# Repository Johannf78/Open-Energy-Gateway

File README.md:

# AmpX Open Energy Gateway

A comprehensive ESP32-based energy monitoring gateway that communicates with Meatrol Brand energy meters via Modbus protocols (RS485 and TCP/IP). The system collects data from up to 32 meters simultaneously, displays it through a web interface, and uploads measurements to a remote API for centralized monitoring.

**Buy ready-built hardware:** <a href="https://ampx.co/product/ampx-energy-gateway/" target="_blank" rel="noopener noreferrer">AmpX Energy Gateway</a> on ampx.co — DIN-rail unit with WiFi, RS485 or TCP/IP Modbus, and uploads to <a href="https://ampx.app" target="_blank" rel="noopener noreferrer">ampx.app</a>.

## 🌟 Features

### Core Capabilities
- **Multi-Protocol Support**: Compatible with both Modbus RS485 and Modbus TCP/IP communication
- **Multi-Meter Support**: Monitor up to 32 energy meters simultaneously
- **Real-Time Web Interface**: Live data display with WebSocket updates
- **API Integration**: Automatic data upload to AmpX Portal every 30 seconds
- **Auto-Discovery**: Automatic detection of connected meters
- **Dual Hardware Variants**: Separate builds for RS485 and TCP/IP configurations

### Hardware Integration
- **ESP32 Wroom 32U**: Main microcontroller platform
- **RS485 Interface**: MAX485 module for serial communication
- **Ethernet Interface**: W5500 Lite for TCP/IP communication
- **Status Indicators**: Four LEDs for system status monitoring
- **WiFi Support**: Wireless connectivity with WiFiManager

### Data Management
- **Real-Time Monitoring**: 3-second update intervals for web interface
- **Scheduled Uploads**: 30-second intervals for API data transmission
- **JSON Data Format**: Structured data exchange and storage
- **Meter Identification**: Unique serial number tracking for each meter

## ☁️ AmpX Energy Portal

View gateway and meter data in the cloud at <a href="https://ampx.app/" target="_blank" rel="noopener noreferrer">https://ampx.app/</a>.

The portal lets you manage gateways, inspect live and historical readings (voltage, current, power, and energy per phase), and export CSV for reporting. The firmware uploads a timestamped snapshot about every 30 seconds.

The portal can be **white-labelled** for your company or resellers (your branding, your domain). Data can also be **customised** and sent to **any portal or platform**, in **any format** you require. Contact AmpX if you need a branded instance or a custom integration.

## 🏗️ Architecture

```
┌─────────────────┐    ┌──────────────────┐    ┌─────────────────┐
│   Energy Meters │    │  AmpX Gateway    │    │   AmpX Portal   │
│                 │    │                  │    │                 │
│ Meatrol Meters  │◄──►│ ESP32 + Modbus   │◄──►│ Remote API      │
│ (RS485/TCP-IP)  │    │ Web Interface    │    │ Data Storage    │
│ Up to 32 units  │    │ Data Processing  │    │ Analytics       │
└─────────────────┘    └──────────────────┘    └─────────────────┘
```

## 📋 Hardware Requirements

### Base Components
- **ESP32 Wroom 32U** microcontroller
- **Power Supply**: 3.3V regulated power
- **Status LEDs**: 5x LEDs for system monitoring (Power, Meter, WiFi, Internet, Server)

### RS485 Configuration
- **MAX485 Interface Module**
- **RS485 Cable**: For meter communication
- **Pull-up/Pull-down Resistors**: 120Ω termination resistors

### TCP/IP Configuration
- **W5500 Lite Ethernet Module**
- **Ethernet Cable**: CAT5/CAT6 network connection
- **Network Switch/Router**: For meter and internet connectivity

## 🚀 Installation

### Prerequisites
- [Arduino IDE](https://www.arduino.cc/en/software) (recommended)
- In Arduino IDE, add this under `File -> Preferences -> Additional Board Manager URLs`:  
  `https://raw.githubusercontent.com/espressif/arduino-esp32/gh-pages/package_esp32_index.json`
  Then install `esp32` from `Tools -> Board -> Boards Manager`.
- ESP32 Board Package for Arduino IDE
- USB-to-UART driver for your ESP32 board (CP210x VCP driver): [Silicon Labs CP210x USB to UART Bridge VCP Drivers](https://www.silabs.com/developers/usb-to-uart-bridge-vcp-drivers)
- Required Arduino libraries (see Dependencies section)

### Quick Start

1. **Clone the Repository**
   ```bash
   git clone https://github.com/Johannf78/Open-Energy-Gateway.git
   cd Open-Energy-Gateway
   ```

2. **Open the Project**
   - **Arduino IDE** (recommended): Open `src/open_energy_gateway/open_energy_gateway.ino`
   - Alternative - PlatformIO: Open the project folder

3. **Configure Hardware Type**
   
   In `open_energy_gateway.ino`, set the communication type:
   ```cpp
   #define MODBUS_TYPE MODBUS_TYPE_RS485  // For RS485 version
   // OR
   #define MODBUS_TYPE MODBUS_TYPE_TCPIP  // For TCP/IP version
   ```

4. **Install USB Driver (Required)**
   - Most ESP32 development boards use a CP210x USB-to-UART bridge chip
   - Install the CP210x VCP driver from Silicon Labs:  
     [https://www.silabs.com/developers/usb-to-uart-bridge-vcp-drivers](https://www.silabs.com/developers/usb-to-uart-bridge-vcp-drivers)
   - On the Silicon Labs download list (Windows), select **CP210x Windows Drivers**
   - Reconnect the board after driver installation so the serial COM port is detected

5. **Upload to ESP32**
   - Connect your ESP32 via USB
   - Select the correct board and port
   - Compile and upload the code

### Dependencies

The following libraries are required:
```cpp
#include <WiFi.h>              // ESP32 built-in WiFi
#include <WebServer.h>         // ESP32 built-in web server
#include <WebSocketsServer.h>  // Real-time updates (by Markus Sattler)
#include <ArduinoJson.h>       // JSON processing (by Benoit Blanchon)
#include <HTTPClient.h>        // ESP32 built-in HTTP client
#include <WiFiManager.h>       // WiFi configuration (by tzapu)
#include <Preferences.h>       // ESP32 built-in NVS storage
#include <HardwareSerial.h>    // ESP32 built-in serial communication
#include <time.h>              // ESP32 built-in time functions
```

### Custom Libraries (Required)
The project requires custom AmpX Modbus libraries available at:
**Repository**: [https://github.com/Johannf78/AmpXModbus](https://github.com/Johannf78/AmpXModbus)

- **For RS485**: `ampx_modbus_rs485.h` 
- **For TCP/IP**: `ampx_modbus_tcpip.h`

**Installation**:
1. Clone or download the AmpXModbus repository
2. Copy the library folders to your Arduino libraries directory:
   `Documents/Arduino/libraries/`

## 🔧 Configuration

### WiFi Setup
On first boot, the device creates a WiFi access point:
- **SSID**: `AmpX-Energy-Gateway-AP`
- **Password**: None (open network)
- Connect and configure your WiFi credentials through the captive portal

### Meter Configuration
Meters are automatically discovered during startup. The system supports:
- **Meter Addresses**: 1-32 (configurable)
- **Baud Rate**: 9600 (RS485)
- **Data Bits**: 8
- **Parity**: None
- **Stop Bits**: 1

### API Configuration
The system supports dual API endpoints (configurable in `open_energy_gateway.ino`):
```cpp
// Local: LAN IP of the PC running XAMPP (port 80). Update when the PC IP changes.
const char* ampxportal_server_local = "http://192.168.2.120/api/v3/";
const char* ampxportal_server_live = "https://ampx.app/api/v3/";
const char* ampxportal_api_key = "...";  // must match AMPX_API_KEY in api/config/config.php
#define USE_LOCAL_SERVER false  // true = LAN XAMPP /api/v3/; false = live /api/v3/
```

Every upload sends header `X-AmpX-Api-Key` (firmware **1.0.3+**). Full API docs: `ampx.app/api/README.md`.

**Breaking changes:** If the portal/API contract changes so older flashed gateways fail, bump `FIRMWARE_VERSION` in the same change and publish OTA before (or with) the live API cutover. The API key requirement is one such break (pre-1.0.3 → 401).

**Local development stack (verified July–August 2026):**
- API: XAMPP at `D:\xampp\htdocs\ampx.app\api\` — firmware posts `POST /api/v3/` (Cloud). Header `X-AmpX-Api-Key` (see that folder’s `README.md`)
- Portal UI: http://ampx-app.local/ (WordPress vhost; not the public Cloudflare `ampx.app` host)
- InfluxDB (legacy v2 path): `influxdb2.ampx.app` via `POST /api/v2/`
- InfluxDB (portal + v3): managed **Cloud Serverless** — account AmpX / org **Energy Gateway** — host `https://eu-central-1-1.aws.cloud2.influxdata.com` (AWS Frankfurt); see `ampx.app/api/README.md`
- Postman: `http://ampx-app.local/api/v2/` or `http://127.0.0.1/api/v2/` — enable header `X-AmpX-Api-Key`
- ESP must reach the PC on TCP **80**; Windows Wi‑Fi profile should be **Private** with Apache firewall allow rules
- Do not use port **8080** unless a separate Docker API is running

**Live stack (verified August 2026 Cloud cutover):**
- API: `https://ampx.app/api/v3/` — `#define USE_LOCAL_SERVER false` (v2 still on Influx 2 until sunset)
- Portal UI: https://ampx.app/ → Meters → gateway → View Data (Cloud / InfluxQL, plugin 1.1.5)
- WordPress `wp-config.php` `AMPX_INFLUXDB_*` → Cloud Serverless; **ORG** = `Energy Gateway` (not AmpX)
- After editing live `wp-config.php` on Hetzner: flush PHP OPcache
- Create/assign the gateway in WP Admin; Influx data alone does not register it in the portal list
- OTA: live `version.json` is **1.0.9** (v2). Next publish is **1.1.1**. Do not publish 1.0.9.

## 💻 Usage

### Web Interface
1. Connect to your local network
2. Find the ESP32's IP address (displayed on serial monitor)
3. Open `http://[ESP32_IP_ADDRESS]` in your browser
4. View real-time meter data in tabular format

### Data Format
The system collects and transmits:
- **Meter Serial Numbers**: Unique identification
- **Energy Measurements**: kWh, kW, Voltage, Current
- **Timestamps**: Measurement time
- **Status Information**: Connection and error states

### API Integration
Data is automatically uploaded to the AmpX Portal every 30 seconds in JSON format:
```json
{
  "gateway_id": "100001",
  "meter_id": "1",
  "serial_number": "12345678",
  "timestamp": "2024-01-15T10:30:00Z",
  "values": {
    "serial": "12345678",
    "voltage_L1": "230.1",
    "current_L1": "24.6",
    "active_power_tot": "5.67",
    "active_energy_imported_tot": "1234.56"
  }
}
```

## 🛠️ Development

### Project Structure
```
Open-Energy-Gateway/
├── src/
│   └── open_energy_gateway/
│       ├── open_energy_gateway.ino       # Main application
│       ├── functions.ino                 # NVS utilities
│       ├── functions_modbus.ino          # Modbus communication
│       ├── functions_web.ino             # Web interface & WebSocket
│       ├── functions_wifi.ino            # WiFi management
│       ├── functions_ethernet.ino        # Ethernet initialization
│       ├── functions_meter.ino           # Meter register definitions
│       ├── functions_api.ino             # API communication
│       ├── functions_ntp.ino             # Time synchronization
│       ├── functions_ota.ino             # HTTP pull OTA (Admin)
│       ├── meter_registers.h             # Register definitions
│       ├── webpage.h                     # HTML templates
│       ├── web_admin.h                   # Admin interface
│       ├── web_settings.h                # Settings page
│       ├── data/                         # Web assets (future SPIFFS option)
│       │   ├── index.html
│       │   ├── settings.html
│       │   ├── admin.html
│       │   └── meter_registers_meatrol.json
│       └── tools/                        # SPIFFS tools (future use)
│           ├── create_spiffs.bat
│           ├── upload_spiffs.bat
│           └── spiffsgen.py
├── memory-bank/                          # Project documentation
├── Documentation/                        # User documentation
└── README.md
```

### Building Different Variants
- **RS485 Version**: Set `MODBUS_TYPE_RS485`
- **TCP/IP Version**: Set `MODBUS_TYPE_TCPIP`

### Debugging
Enable debug output by defining:
```cpp
#define DEBUG 1
```

### Web Interface Implementation
Currently, the web interface is implemented using header files containing HTML templates:

- **webpage.h**: Main dashboard HTML template
- **web_settings.h**: Settings page HTML template  
- **web_admin.h**: Admin page HTML template

The templates use string replacement for dynamic content (meter serial numbers, values, etc.).

### Future SPIFFS Option
The project includes infrastructure for future SPIFFS implementation:

1. **SPIFFS Tools Available** (not currently used):
   ```bash
   cd src/open_energy_gateway/tools
   create_spiffs.bat  # Future: Create SPIFFS image
   upload_spiffs.bat  # Future: Upload to ESP32
   ```

2. **Web Assets Ready** in `data/` folder for future SPIFFS deployment

### Current Limitations
- **Active Meters**: Currently configured for 5 meters (backend expandable; HTML rows needed beyond that)
- **Server URLs**: API and OTA hosts (`ampxportal_server_local` / `_live`, `USE_LOCAL_SERVER`, firmware URLs) require a firmware rebuild
- **Gateway ID**: Changeable from Admin; stored in NVS (`DEFAULT_GATEWAY_ID` is first-boot only)
- **OTA Updates**: Admin HTTP pull from `https://ampx.app/firmware/` (Check + Update); first flash USB with 8MB dual-OTA partitions; sketch **1.1.1** (live `/api/v3/`); next OTA publish **1.1.1** — do not publish **1.0.9** (still v2)
- **Admin Interface**: Gateway reboot (LEDs off first) + OTA + Clear WiFi (ship-mode); Gateway ID change with password

### Shipping a gateway
1. Set Gateway ID on Admin (if not already assigned in the portal).
2. Open **Admin → Clear WiFi (Ship Mode)**, enter the admin password, confirm.
3. Confirm the open AP `energy-gateway-{ID}` appears (no workshop SSID).
4. Box the unit. At the site, the customer joins that AP, opens **http://192.168.4.1**, saves their WiFi, then opens `http://energy-gateway-{ID}.local` or the IP from their router.
5. Do not leave workshop WiFi stored on a unit that will be shipped.

## 🔍 Troubleshooting

### Common Issues

**No Meter Communication**
- Check wiring connections
- Verify meter addresses (1-32)
- Ensure proper termination resistors (RS485)
- Check network connectivity (TCP/IP)

**Web Interface Not Loading**
- Verify ESP32 is connected to WiFi
- Check IP address in serial monitor
- Ensure port 80 is not blocked

**Web UI Stuck on “Connecting…” (WebSocket)**

The page is served over HTTP (port 80). **Connection status: Connecting…** means the browser is waiting for the WebSocket on **port 81** (`ws://hostname:81/`). The HTTP page can load while the WebSocket is still down.

**Cause:** Modbus reads block the ESP32. The WebSocket on port 81 is only accepted when `webSocket.loop()` runs. On TCP, each register used to open and close port 502, so the first page could sit on Connecting for up to about 40 seconds.

**Current pattern (Sep 2026):** one Modbus TCP socket for the whole sweep, closed once at the end of `handlePowerMeter()`. `server.handleClient()` and `webSocket.loop()` run before every register read, and `handleWebSocket()` sends the JSON once after the sweep. Bench measurement before a leftover 100 ms pause was removed: about 5 seconds. There is no per-register `delay(100)`; `modbus_read_response()` already waits up to 2 seconds for the frame.

Also keep `server.handleClient()` / `webSocket.loop()` at the end of `loop()`. Do not call `reconnectMeter()` / `initEthernet()` from the 1-second meter path (`initEthernet()` waits 2 seconds and freezes the page).

**Boot delay (separate from the meter sweep):** Before `loop()` runs, `setup()` may wait on NTP (up to about 15 seconds). The web server does not handle clients until `setup()` finishes.

**Cannot Connect to Setup Hotspot (Windows)**

On first boot (or when no WiFi credentials are saved), the gateway creates an open access point named `energy-gateway-{GATEWAY_ID}` (for example `energy-gateway-100001`). Connect to this network and open **http://192.168.4.1** to configure WiFi.

**Problem:** Windows shows as connected to the hotspot, but the PC does not receive an IP address (often `169.254.x.x` instead of `192.168.4.x`), so the setup page cannot be opened. The Windows Settings UI may still show “IP assignment: Automatic (DHCP)” even when DHCP is not actually active on the adapter.

**Solution:**
1. Confirm in Command Prompt with `ipconfig /all` that the Wi‑Fi adapter shows **DHCP Enabled: Yes**.
2. If it shows **No**, enable DHCP from an elevated Command Prompt or PowerShell:
   ```
   netsh interface ip set address name="WiFi 3" dhcp
   netsh interface ip set dns name="WiFi 3" dhcp
   ```
   Replace `WiFi 3` with your adapter name from `ipconfig` if different.
3. Disconnect and reconnect to the gateway hotspot, then check that you have an address such as `192.168.4.2` and gateway `192.168.4.1`.
4. Open **http://192.168.4.1** in a browser.

**Workaround:** If DHCP still fails, set a temporary static IP on the Wi‑Fi adapter: IP `192.168.4.10`, subnet mask `255.255.255.0`, gateway `192.168.4.1`.

**API Upload Failures**
- Serial success looks like: `HTTP Response Code: 201` and `Data stored successfully`
- HTTP **401**: `ampxportal_api_key` must match `AMPX_API_KEY` in `api/config/config.php` (local already enforces this)
- `connection refused` (-1) to the PC IP: check Windows Firewall / Wi‑Fi **Private** profile; Apache must accept LAN inbound on port 80 (not only localhost)
- Confirm `ampxportal_server_local` matches the PC’s current LAN IP and uses `/api/v3/` on port 80 (local Cloud path)
- Confirm InfluxDB is healthy (`https://influxdb2.ampx.app/health`) — API returns 500 if storage fails
- View data (local): http://ampx-app.local/ → Meters → gateway → View Data
- View data (live): https://ampx.app/ → Meters → gateway → View Data (needs WP gateway assignment + `AMPX_INFLUXDB_*` in live `wp-config.php`)
- Misleading firmware message: “No internet connection” on connection-refused may mean LAN blocked, not WAN down

**Admin OTA reboot / Checking… stuck**
- Serial `rst:0x8 (TG1WDT_SYS_RESET)` after `Fetching firmware manifest:` = old firmware (≤1.0.5) putting `WiFiClientSecure` on the `loop()` stack — USB-flash or OTA **1.0.7+**
- Opening Admin must not fetch; only **Check for update** starts HTTPS
- Serial Monitor baud is **115200**
- Live files: `https://ampx.app/firmware/version.json` and the `.bin` must both be published and versions aligned

**Live portal “critical error” on Meters**
- Check Debug Log Manager log (path in `WP_DEBUG_LOG`), not only Apache `www_logs`
- Common cause: missing `AMPX_INFLUXDB_*` constants in live `wp-config.php`
- If constants were just added and error persists: flush PHP OPcache

**NTP `TIMEOUT!` on boot**
- `initNTP()` waits up to a max (currently ~15s) and exits early on success; increase the timeout if sync still fails
- Check router/firewall allows outbound NTP (UDP/123)

### Status LED Indicators
- **LED 1 (Power - Pin 12)**: System power status
- **LED 2 (Meter - Pin 14)**: Meter communication status  
- **LED 3 (WiFi - Pin 27)**: WiFi connection status
- **LED 4 (Internet - Pin 26)**: Internet connectivity status
- **LED 5 (Server - Pin 25)**: API server communication status

## 🤝 Contributing

We welcome contributions! Please follow these steps:

1. Fork the repository
2. Create a feature branch (`git checkout -b feature/amazing-feature`)
3. Commit your changes (`git commit -m 'Add amazing feature'`)
4. Push to the branch (`git push origin feature/amazing-feature`)
5. Open a Pull Request

### Development Guidelines
- Follow Arduino coding standards
- Test with actual hardware when possible
- Update documentation for new features
- Maintain backwards compatibility

## 📄 License

This project is licensed under the MIT License - see the [LICENSE](LICENSE) file for details.

## 🏢 Commercial Use

This project is designed for industrial and commercial energy monitoring applications:
- **Manufacturing Facilities**: Multi-zone energy monitoring
- **Commercial Buildings**: Tenant energy tracking
- **Energy Auditing**: Standardized data collection
- **Remote Monitoring**: Centralized meter management

## 📞 Support

- **Contact AmpX**: <a href="https://ampx.co/contact/" target="_blank" rel="noopener noreferrer">ampx.co/contact</a> — product questions, quotes, and commercial support
- **Issues**: [GitHub Issues](https://github.com/Johannf78/Open-Energy-Gateway/issues)
- **Documentation**: See `memory-bank/` folder for detailed technical documentation
- **Hardware Support**: Compatible with Meatrol Brand energy meters

## 🙏 Acknowledgments

- ESP32 Community for excellent documentation and libraries
- Modbus community for protocol specifications
- Contributors to the WebSocket and WiFiManager libraries

---

**Built with ❤️ for the energy monitoring community**

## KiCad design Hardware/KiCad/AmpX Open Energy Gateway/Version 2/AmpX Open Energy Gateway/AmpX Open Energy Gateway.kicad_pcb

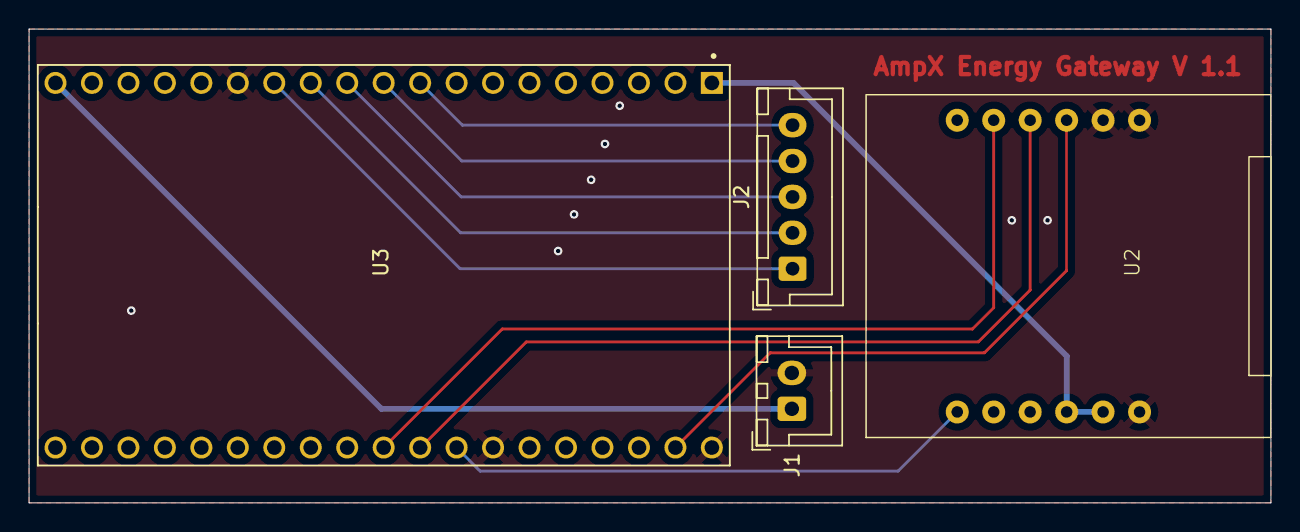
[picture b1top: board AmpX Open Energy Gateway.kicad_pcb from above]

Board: 2 copper layers, 86.5 x 33.0 mm, 4 parts (0 on the bottom side), 12 nets.

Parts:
J1: POW; JST_XH_B2B-XH-A_1x02_P2.50mm_Vertical
J2: STATUS; JST_XH_B5B-XH-A_1x05_P2.50mm_Vertical
U2: W5500; Module_Ethernet_LAN_W5500_Lite
U3: ESP32-DEVKITC-32U; MODULE_ESP32-DEVKITC-32U

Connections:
+3.3V: U2.4 (VCC), U2.5 (VCC), U3.1 (3V3)
/+5V: J1.1, U3.19 (EXT_5V)
/CS: U2.11 (CS), U3.29 (IO5)
/GND: J1.2, U2.6 (GND), U2.7 (GND), U2.8 (GND), U3.14 (GND1), U3.32 (GND2), U3.38 (GND3)
/INTERNET: J2.4, U3.10 (IO26)
/METER: J2.2, U3.12 (IO14)
/MISO: U2.1 (MISO), U3.31 (IO19)
/MOSI: U2.9 (MOSI), U3.37 (IO23)
/POWER: J2.1, U3.13 (IO12)
/SCLK: U2.10 (SCK), U3.30 (IO18)
/SERVER: J2.5, U3.9 (IO25)
/WIFI: J2.3, U3.11 (IO27)

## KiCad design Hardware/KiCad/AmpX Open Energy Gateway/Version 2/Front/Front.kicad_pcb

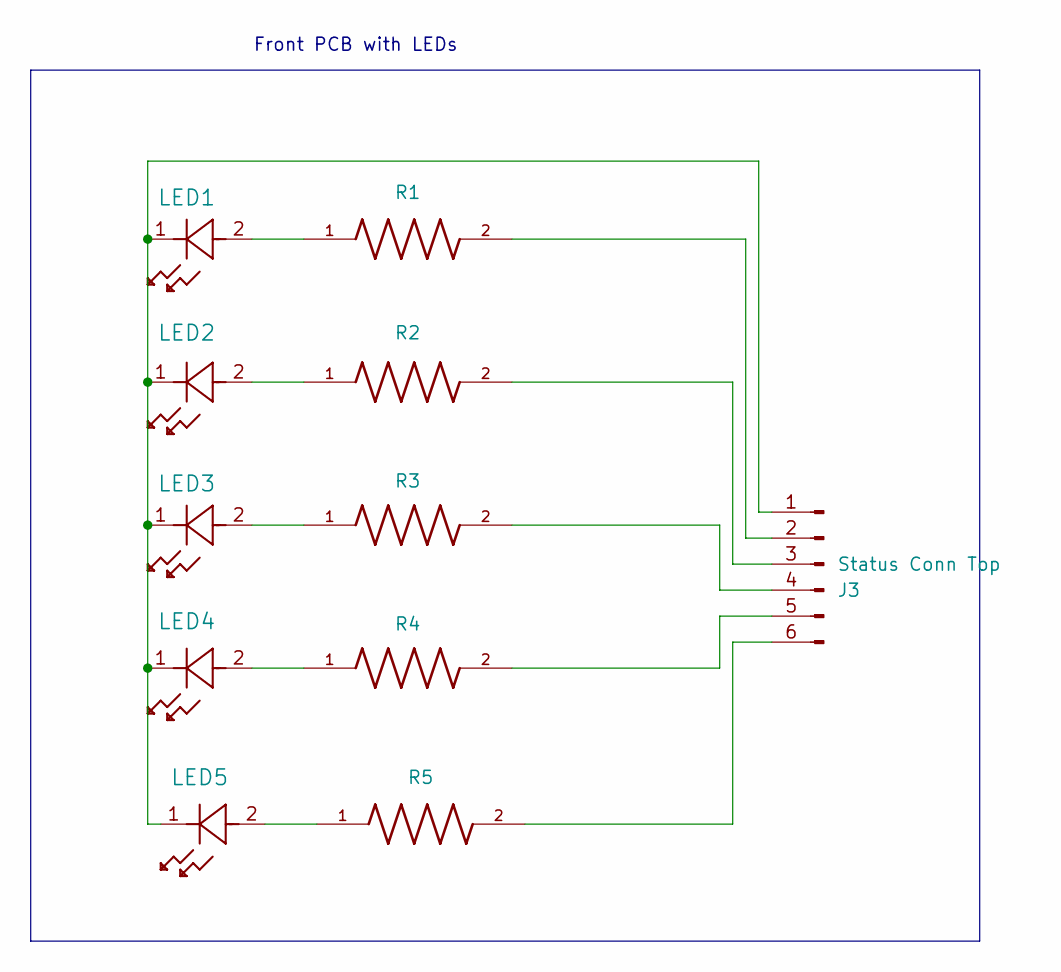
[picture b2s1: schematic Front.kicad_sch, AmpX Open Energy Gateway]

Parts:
J3: Status Conn Top; SolderWire-0.5sqmm_1x06_P4.6mm_D0.9mm_OD2.1mm
LED1, LED2, LED3, LED4, LED5: CMD15-21VGD/TR8; LED_GREEN_CMD15-21_VCC
R1, R2, R3, R4, R5: Resistor SMD DigiKey ERJ-T06J221V; Resistor_SMD_Digikey_RESC2012X70N

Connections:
unnamed: J3.1, LED1.1, LED2.1, LED3.1, LED4.1, LED5.1
unnamed: J3.2, R1.2
unnamed: J3.3, R2.2
unnamed: J3.4, R3.2
unnamed: J3.5, R4.2
unnamed: J3.6, R5.2
unnamed: LED1.2, R1.1
unnamed: LED2.2, R2.1
unnamed: LED3.2, R3.1
unnamed: LED4.2, R4.1
unnamed: LED5.2, R5.1

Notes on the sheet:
Front PCB with LEDs

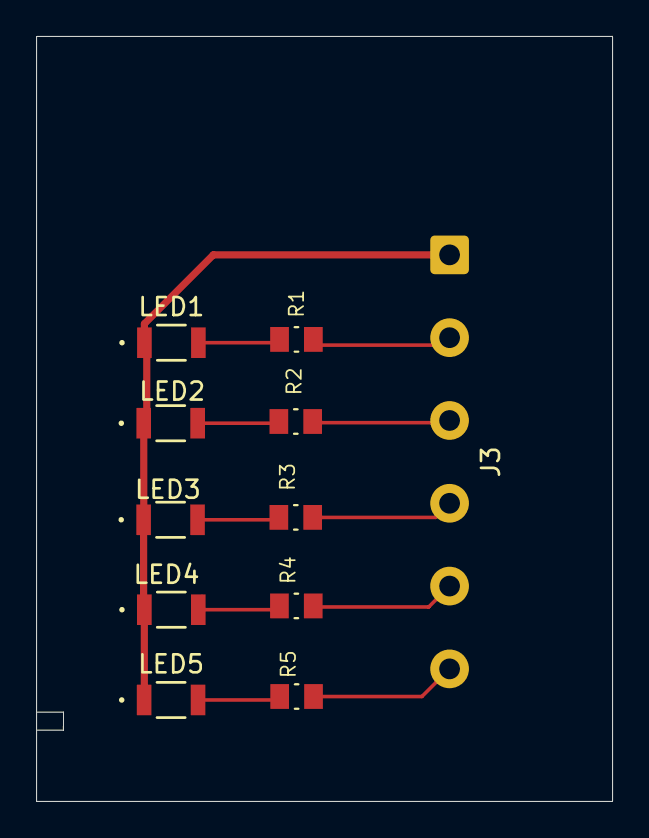
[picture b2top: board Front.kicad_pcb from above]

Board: 2 copper layers, 32.0 x 42.5 mm, 11 parts (0 on the bottom side), 11 nets.

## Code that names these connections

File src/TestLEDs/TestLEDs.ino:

/*
  Blink

  Turns an LED on for one second, then off for one second, repeatedly.
  Test leds for the Open energy gateway.

Before compiling
1. Select the correct port and board.
2. Set the correct serial port boad rate: 115200
3. Set the correct flash size, 4MB or 8MB
4. Set the correct partition format.
*/

//Define the status indicating LEDs pins
//                        //XIAO//WROOM
#define LED_1_POWER     12 //2   //12 //Indicates Power is on 
#define LED_2_METER     14 //3   //14 //Indicates Meter is connected via Modbus
#define LED_3_WIFI      27 //4   //27 //Indicates WiFi is connected
#define LED_4_INTERNET  26 //5   //26 //Indicates Internet is connected, this is the green LED
#define LED_5_SERVER    25 //6   //25 //Indicates succesfull communication with the Server


void setup() {
  // initialize LED status pins as outputs.
  pinMode(LED_1_POWER, OUTPUT);
  pinMode(LED_2_METER, OUTPUT);
  pinMode(LED_3_WIFI, OUTPUT);
  pinMode(LED_4_INTERNET, OUTPUT);
  pinMode(LED_5_SERVER, OUTPUT);

  Serial.begin(115200); // Initialize serial communication
  delay(2000); //Wait for the serial port te become available.
  Serial.println("");
  Serial.println("");

  Serial.print("LED_1_POWER: ");
  Serial.println(LED_1_POWER);

  Serial.print("LED_2_METER: ");
  Serial.println(LED_2_METER);

  Serial.print("LED_3_WIFI: ");
  Serial.println(LED_3_WIFI);

  Serial.print("LED_4_INTERNET: ");
  Serial.println(LED_4_INTERNET);

  Serial.print("LED_5_SERVER: ");
  Serial.println(LED_5_SERVER);
  Serial.println("");

  Serial.print("Flash Chip Size: ");
  Serial.println(ESP.getFlashChipSize()); // Get flash size in bytes
  
  Serial.print("Chip Model: ");
  Serial.println(ESP.getChipModel()); 

  Serial.print("Chip Revision: ");
  Serial.println(ESP.getChipRevision()); 

  Serial.print("Chip Cores: ");
  Serial.println(ESP.getChipCores()); 
}


void loop() {
  
  digitalWrite(LED_1_POWER, HIGH);
  delay(200);
  digitalWrite(LED_2_METER, HIGH);
  delay(200);
  digitalWrite(LED_3_WIFI, HIGH);
  delay(200);
  digitalWrite(LED_4_INTERNET, HIGH);
  delay(200);
  digitalWrite(LED_5_SERVER, HIGH);
  delay(200);

  //digitalWrite(LED_1_POWER, LOW);
  delay(200);
  //digitalWrite(LED_2_METER, LOW);
  delay(200);
  //digitalWrite(LED_3_WIFI, LOW);
  delay(200);
  //digitalWrite(LED_4_INTERNET, LOW);
  delay(200);
  //digitalWrite(LED_5_SERVER, LOW);
  delay(200);


}

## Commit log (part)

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2025-08-30 Documentation and git ignore
2025-08-30 updated memory bank
2025-09-01 Minor changes
2025-09-02 moved doc
2025-09-17 Added hardware and version
2025-09-18 added new symbols
2025-09-18 updated schmatic, and pcb
2025-09-18 3D models working
2025-09-20 added 3D models
2025-09-20 Implemented Gateway ID on admin page
2025-09-20 added mDNS
2025-09-22 feat: complete pcb design
2025-09-22 fix: modify .gitignore
2025-09-23 small chnages
2025-09-23 Moved KiCad To version folder
2025-09-26 Gerbers
2025-10-13 created gerbers
2025-10-13 webpage_home
2025-10-14 Move to array for meter numbers...
2025-10-14 changed to dynamic meter numbers
2025-10-14 added meter list summary
2025-10-14 width
2025-10-14 Micheal changes
2025-10-15 Added left menu and meter details page
2025-10-15 cursor
2025-10-16 feat: separate front and bottom pcbs
2025-10-16 update webpages
2025-10-17 increased meters to 5, fixed long connection bug of websockets
2025-11-01 added extra wire for ground
2026-03-31 api update
2026-05-27 jf
    jf

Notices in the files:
README.md:
License: MIT
